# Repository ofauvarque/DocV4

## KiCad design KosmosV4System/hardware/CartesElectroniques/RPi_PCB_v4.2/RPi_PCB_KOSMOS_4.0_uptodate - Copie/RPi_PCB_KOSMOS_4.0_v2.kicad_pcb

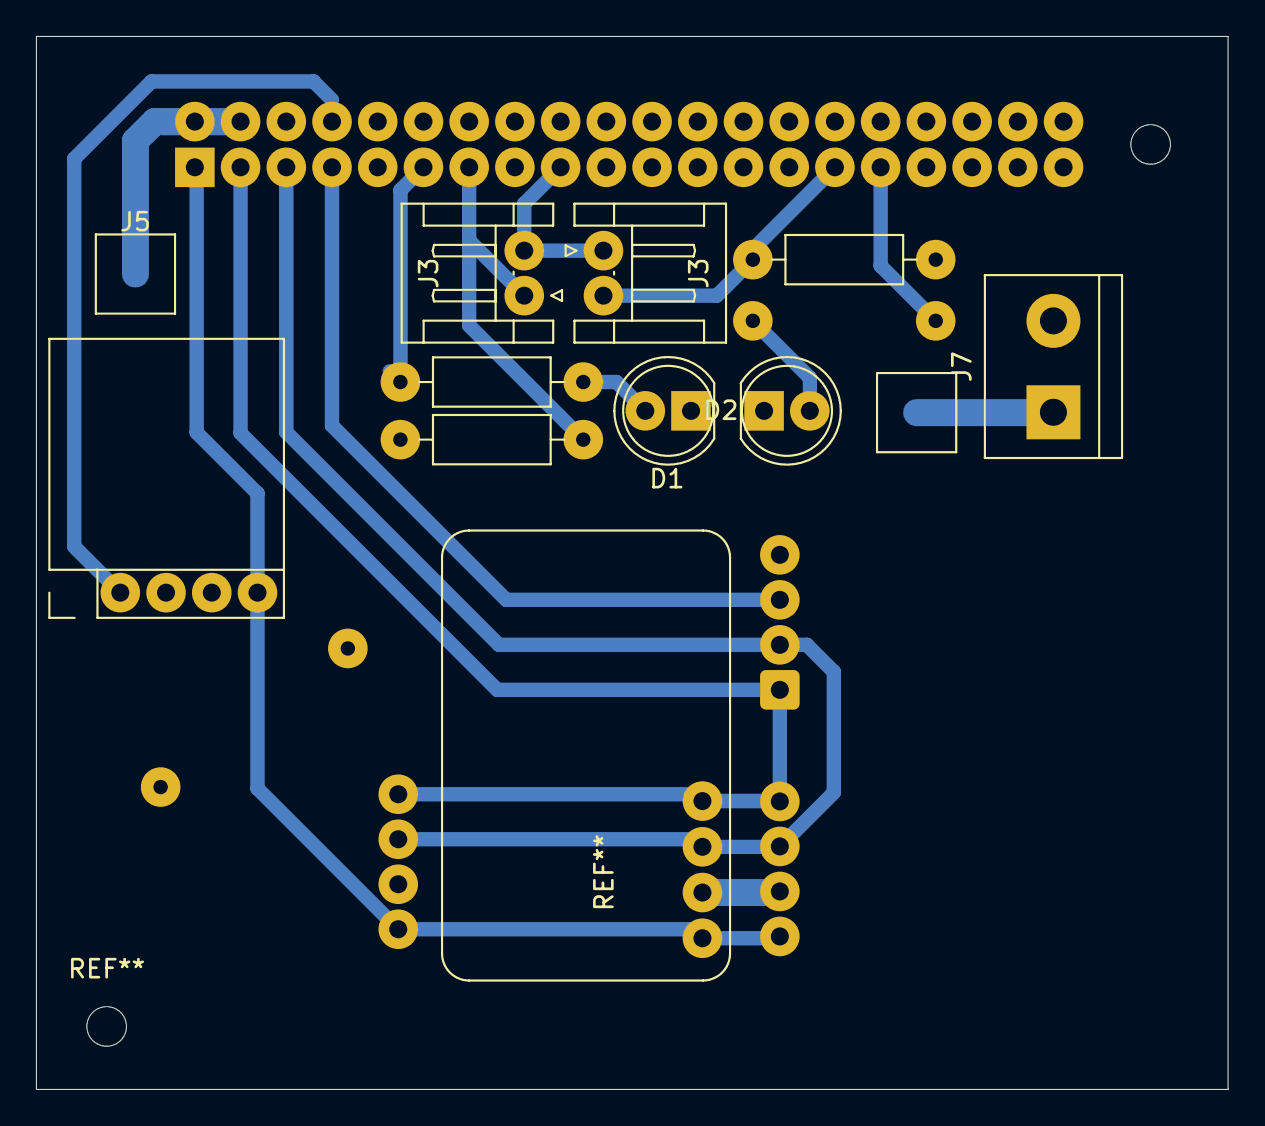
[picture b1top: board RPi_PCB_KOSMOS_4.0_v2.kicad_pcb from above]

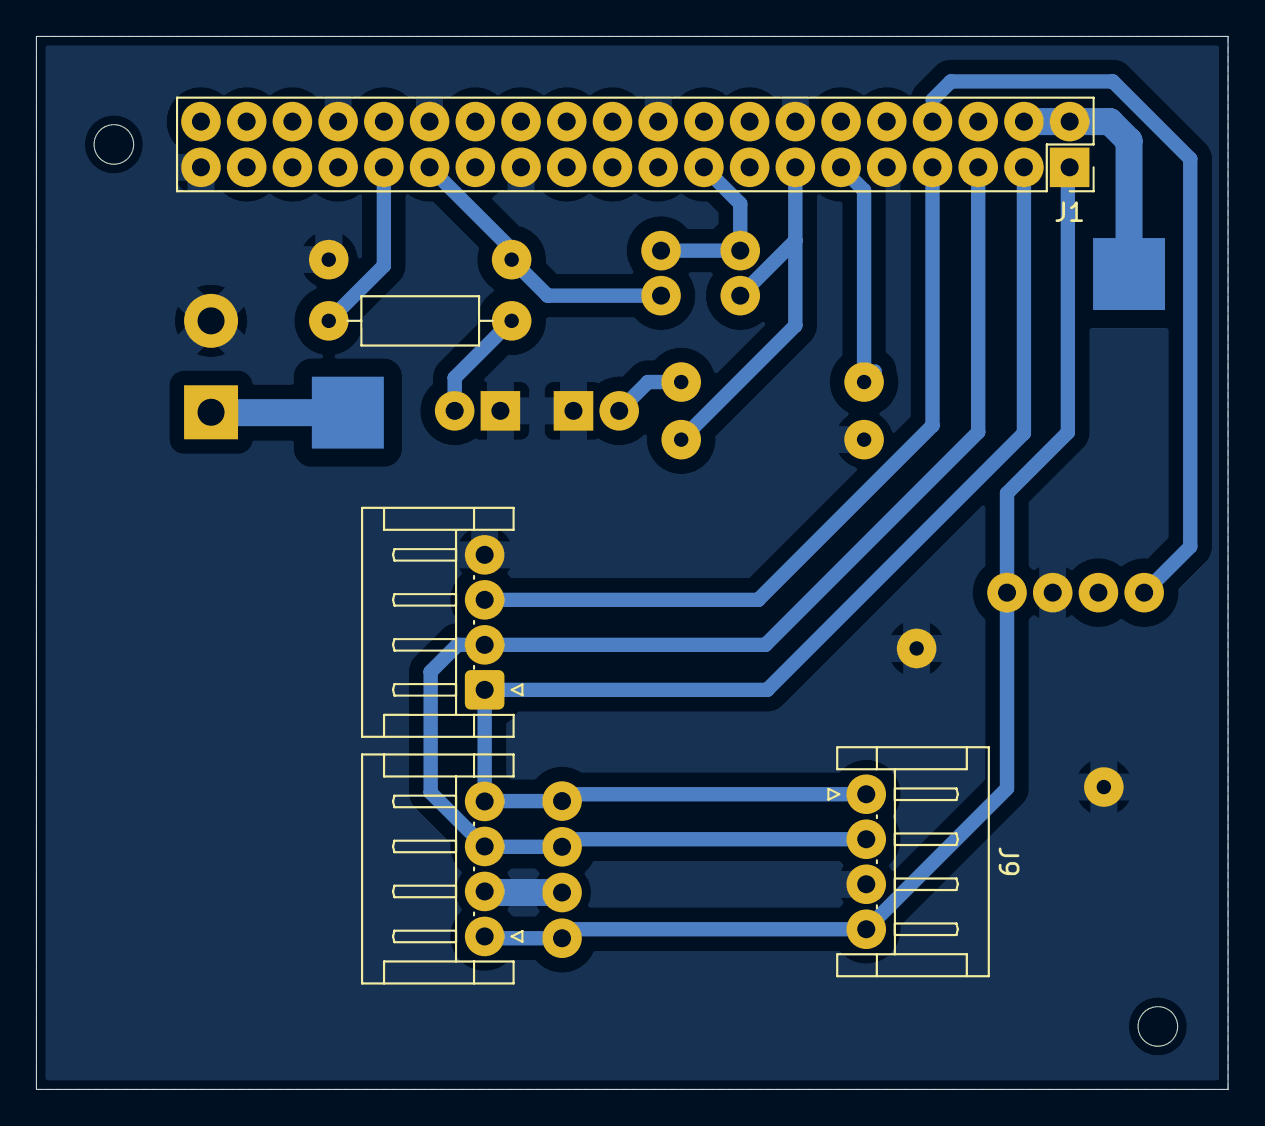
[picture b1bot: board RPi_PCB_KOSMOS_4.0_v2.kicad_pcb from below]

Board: 2 copper layers, 66.2 x 58.5 mm, 16 parts (5 on the bottom side), 15 nets.

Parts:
D1: LED_verte; LED_D5.0mm_v2.2mm
D2: LED_rouge; LED_D5.0mm_v2.2mm
IC1: Module_GPS; GPS_BDS_BeiDou_Dual_Module_v2.2mm
J1: Raspberry_Pi_2_3; PinSocket_2x20_P2.54mm_Vertical_pad2.2mm
J2: Arduino_Motor; JST_EH_S4B-EH_1x04_P2.50mm_Horizontal_kosmos
J3, J3#2: ILS 1; JST_EH_S2B-EH_1x02_P2.50mm_Horizontal_kosmos
J4: Capteur_Temp; JST_EH_S4B-EH_1x04_P2.50mm_Horizontal_kosmos
J5, J6: Conn_01x01_Socket_Solder_Pad; TestPoint_Pad_4.0x4.0mm_KOSMOS
J7: Alim_Principale; TerminalBlock_bornier-2_P5.08mm_v3mm
J9: Capteur_Lux; JST_EH_S4B-EH_1x04_P2.50mm_Horizontal_kosmos
R1, R2: 260; R_Axial_DIN0207_L6.3mm_D2.5mm_P10.16mm_Horizontal_v2.2mm
R3, R4: 10k; R_Axial_DIN0207_L6.3mm_D2.5mm_P10.16mm_Horizontal_v2.2mm

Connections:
+3.3V: IC1.5 (VCC), J1.1 (3V3), J1.17 (3V3), J3.2, J3#2.1, J4.1, J9.4
+5V: J6.1, J7.1
GND: D1.1 (K), D2.1 (K), IC1.4 (GND), J1.6 (GND), J1.9 (GND), J1.14 (GND), J1.20 (GND), J1.25 (GND), J1.30 (GND), J1.34 (GND), J1.39 (GND), J2.4, J4.2, J7.2, J9.3, R3.2, R4.2
GPIO4: J1.7 (GCLK0/GPIO4), J2.3
GPIO5: J1.29 (GCLK1/GPIO5), J3#2.2, R4.1
GPIO6: J1.31 (GCLK2/GPIO6), R2.1
GPIO17: J1.11 (GPIO17), R1.1
GPIO27: J1.13 (GPIO27), J3.1, R3.1
unnamed: D1.2 (A), R1.2
unnamed: D2.2 (A), R2.2
unnamed: J1.2 (5V), J1.4 (5V), J5.1
RX: IC1.3 (TX), J1.10 (GPIO15/RXD)
SCL: J1.5 (SCL/GPIO3), J2.2, J4.3, J9.2
SDA: J1.3 (SDA/GPIO2), J2.1, J4.4, J9.1
TX: IC1.2 (RX), J1.8 (GPIO14/TXD)

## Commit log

2025-01-17 AjoutVuesGenerales
2025-01-17 DocV4enConstruction
2025-01-27 AjoutPhotosPourDoc
2025-01-27 AjoutCAOV4
2025-01-27 MajPhotos
2025-01-28 schéma Elec carte moteur
2025-01-29 AjoutPhotosSemaine2
2025-01-29 MaJ Sourcing
2025-02-05 Maj Session 3 V4 iUEM
2025-02-18 ajout photos
2025-02-20 Photos Batterie et Moteur
2025-02-28 photos caisson principal
2025-03-05 nouveau fichier structuration
2025-03-05 rename dossier
2025-03-05 modifs...
2025-03-05 structuration
2025-03-10 drthdh
2025-03-12 vcwxvcb
2025-03-13 sdfg
2025-03-26 khgjg
2025-03-26 sdqqsf
2025-03-26 ertezgrgerg
2025-03-26 jvjhg
2025-03-27 fgjh
2025-03-27 erty
2025-04-02 afesdfg
2025-04-08 fghj
2025-05-12 iughiou
2025-06-30 Add MagPi
2025-07-15 jfhhfg
2025-07-16 restructuration
2025-07-16 reconstruction
2025-07-16 fgdh
2025-07-21 xcvb
2025-07-23 nouvelles images
2025-07-25 maj sourcing pdf
2025-08-06 Create 02_flanges
2025-08-19 documentation software
2025-08-19 crop image
2025-08-20 capture mode emploi
2025-08-20 kkjh
2025-09-15 version alexandre
2025-09-17 ajout cao v4
2025-09-17 sdfhsdfh
2025-09-26 dfgf
2025-10-03 fgjfgdj
2025-10-10 fgth
2025-10-13 hkkcv
2025-11-30 ojpûiop
2025-12-01 fghjfghj
2025-12-19 jlgjhg
2025-12-22 nbvn
2025-12-23 hfgdh
2025-12-23 dfhsfd
2025-12-23 sfgh
2025-12-23 xfdhfgd
2026-01-06 nettoyage
2026-01-06 dfgt
2026-01-08 dfhfgh
2026-01-08 xcfgh
2026-01-08 dfgh
2026-01-09 fgsfdg
2026-01-09 qfdgsfd
2026-01-09 ghjfgh
2026-01-09 sdfgsfd
2026-01-09 ghfgdh
2026-01-09 qsdf
